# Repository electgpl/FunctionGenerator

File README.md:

# Generador de Funciones con XR2206 v1.0 

# Generador de Funciones con XR2206 v2.0 

Este es un Generador de Señales discreto en base a componentes de fácil adquisición para facilitar la producción para ser ensamblado por los estudiantes.

## Controles - v1.0

  - Generador - **XR2206**
  - Preajuste de Simetría
  - Preajuste de Distorsión
  - Ajuste de Amplitud
  - Ajuste de Ganancia
  - Ajuste de Frecuencia
  - Selección de Rango de Frecuencia mediante Jumper o switch (4 rangos)
  - Selección de salida Triangular o Senoidal mediante Jumper o switch
  - Buffer de Salida
  - Salida BNC de 50R
  - Salida Cuadrada para Frecuencímetro y Sincronismo
  
## Controles - v2.0

  - Generador - **XR2206**
  - Preajuste de Simetría
  - Preajuste de Distorsión
  - Ajuste de Amplitud
  - ~~Ajuste de Ganancia~~
  - Ajuste de Frecuencia
  - Selección de Rango de Frecuencia mediante Jumper o switch ~~(4 rangos)~~ (3 rangos)
  - Selección de salida Triangular o Senoidal mediante Jumper o switch
  - ~~Buffer de Salida~~
  - Salida BNC de 50R
  - Salida Cuadrada para Frecuencímetro y Sincronismo

## Alimentacion

> Diseñado para ser alimentado con una única batería de 9V
> en su interior cuenta con una fuente con masa flotante para lograr la simetría en el amplificador operacional (solo para v1.0).
> El amplificador operacional puede ser reemplazado por cualquiera con entrada FET (Se requiere alta impedancia) (solo para v1.0).

### Diseño

> Diseñado con EAGLE, en solo una capa con componentes THT para facilitar
> la integración al alumno, el desarrollo del PCB en el hogar y mantener
> el menor costo posible.

### Pruebas de Señal Seno y Cuadrada

### Pruebas de FFT sobre Seno

Patrocinado
----

License
----

MIT

**Free Software, Hell Yeah!**

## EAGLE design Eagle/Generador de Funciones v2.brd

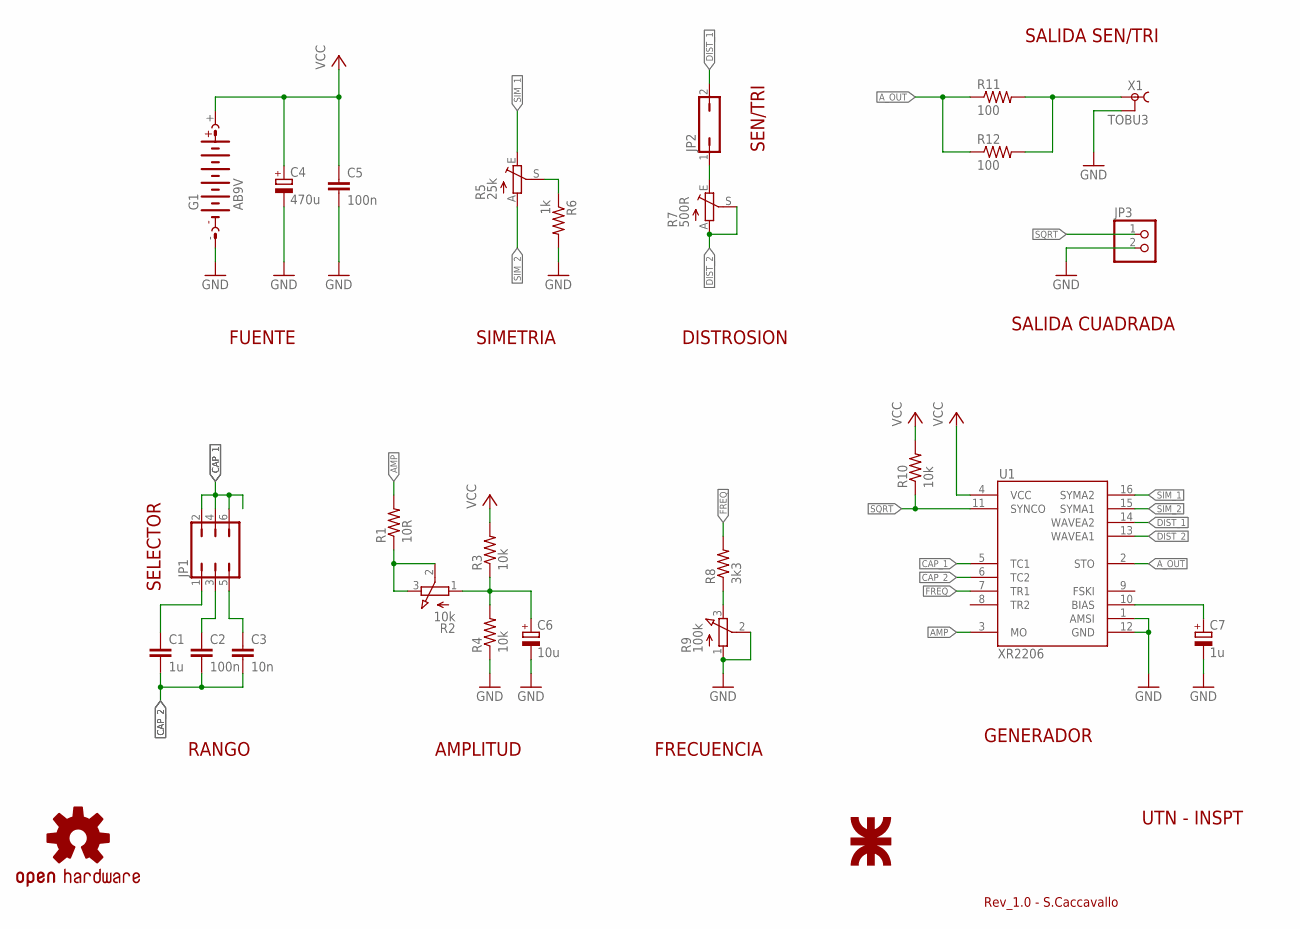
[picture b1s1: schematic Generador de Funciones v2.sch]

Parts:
C1: 1u; C050-024X044
C2, C5: 100n; C050-024X044
C3: 10n; C050-024X044
C4: 470u; E3,5-8
C6: 10u; E2,5-6
C7: 1u; E2,5-6
G1: AB9V
JP1: JP3Q
JP2: JP1Q; JP1
JP3: PINHD-1X2; 1X02
R1: 10R; 0207/10
R2: 10k; 3RP/1610N
R3, R4, R10: 10k; 0207/10
R5: 25k; RJ9W
R6: 1k; 0207/10
R7: 500R; RJ9W
R8: 3k3; 0207/10
R9: 100k; 3RP/1610N
R11, R12: 100; 0207/10
U1: XR2206; DIL16
U$1: UTN_LOGO_0; UTN_LOGO_0_TOP
U$4: OSHW-LOGOM; OSHW-LOGO-M
X1: TOBU3

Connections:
AMP: R1.2, U1.3 (MO)
A_OUT: R11.1, R12.1, U1.2 (STO)
CAP_1: JP1.2, JP1.4, JP1.6, U1.5 (TC1)
CAP_2: C1.2, C2.2, C3.2, U1.6 (TC2)
DIST_1: JP2.2, U1.14 (WAVEA2)
DIST_2: R7.A, R7.S, U1.13 (WAVEA1)
FREQ: R8.2, U1.7 (TR1)
GND: C4.-, C5.2, C6.-, C7.-, G1.-, JP3.2, R4.1, R6.2, R9.1 (A), R9.2 (S), U1.1 (AMSI), U1.12 (GND), X1.2, X1.2@1 (2), X1.2@2 (2)
unnamed: R1.1, R2.2 (S), R2.3 (E)
unnamed: R8.1, R9.3 (E)
unnamed: C1.1, JP1.1
unnamed: C2.1, JP1.3
unnamed: C7.+, U1.10 (BIAS)
unnamed: R5.S, R6.1
unnamed: C3.1, JP1.5
unnamed: R11.2, R12.2, X1.1
unnamed: JP2.1, R7.E
unnamed: C6.+, R2.1 (A), R3.1, R4.2
SIM_1: R5.E, U1.16 (SYMA2)
SIM_2: R5.A, U1.15 (SYMA1)
SQRT: JP3.1, R10.1, U1.11 (SYNCO)
VCC: C4.+, C5.1, G1.+, R3.2, R10.2, U1.4 (VCC)

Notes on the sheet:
RANGO
AMPLITUD
FRECUENCIA
SIMETRIA
DISTROSION
FUENTE
SELECTOR
SEN/TRI
UTN - INSPT
SALIDA SEN/TRI
GENERADOR
SALIDA CUADRADA
Rev_1.0 - S.Caccavallo

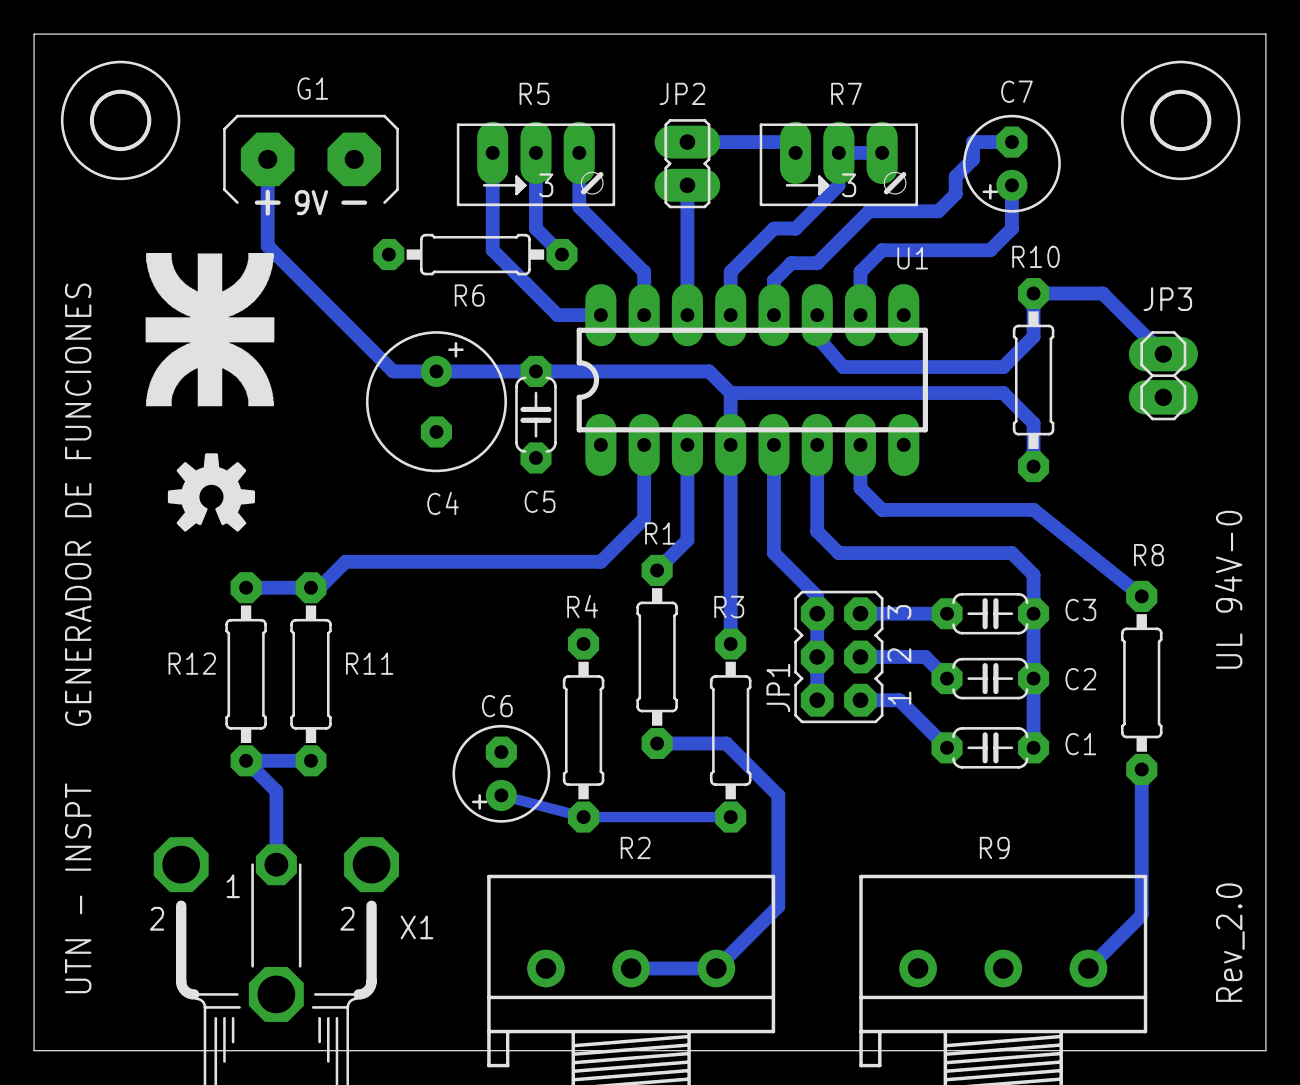
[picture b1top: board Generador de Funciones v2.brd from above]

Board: 2 copper layers, 72.3 x 59.7 mm, 29 parts (0 on the bottom side), 22 nets.

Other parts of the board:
U$2, U$3: 3,2

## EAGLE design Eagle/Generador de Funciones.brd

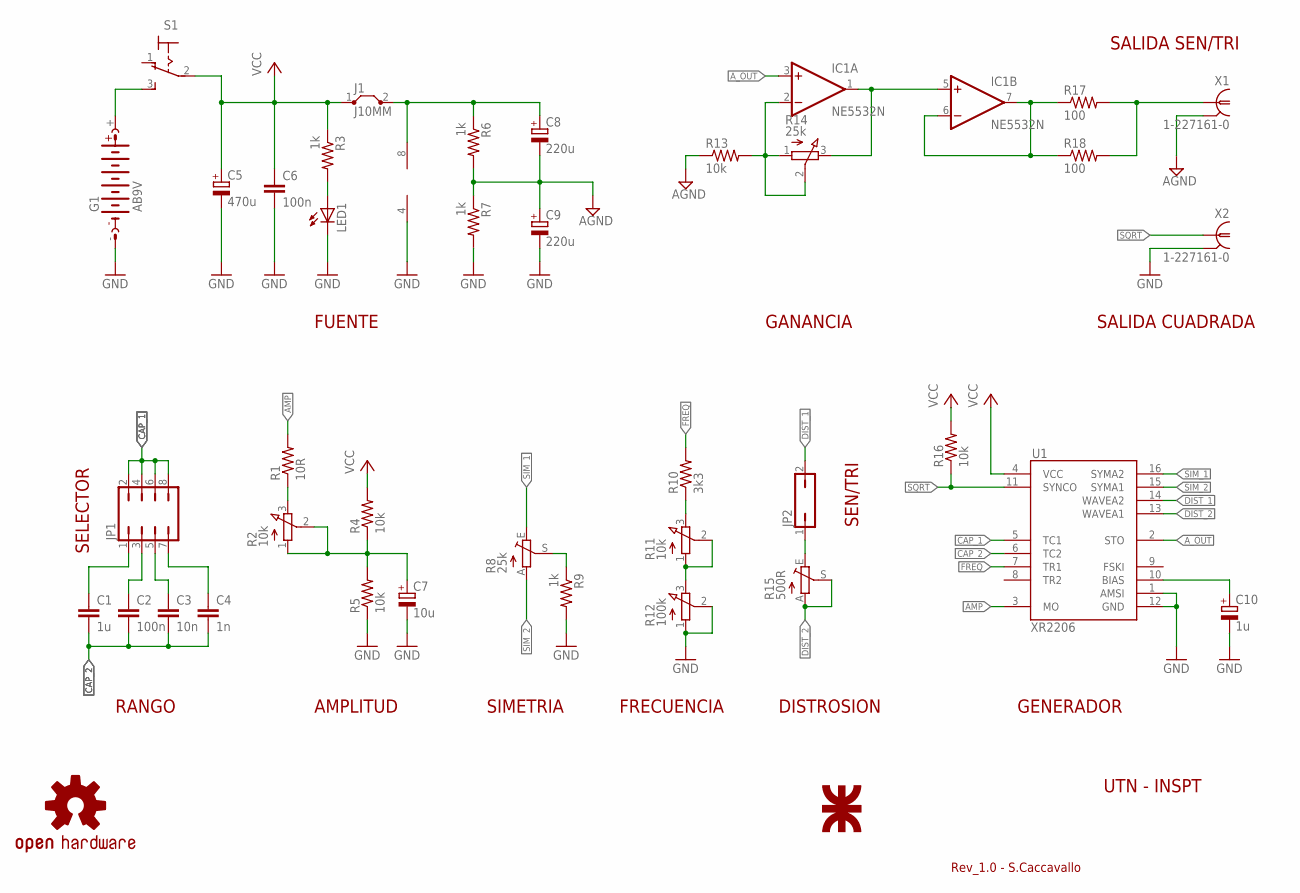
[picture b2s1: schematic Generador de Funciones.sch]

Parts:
C1: 1u; C050-024X044
C2, C6: 100n; C050-024X044
C3: 10n; C050-024X044
C4: 1n; C050-024X044
C5: 470u; E3,5-8
C7: 10u; E2,5-6
C8, C9: 220u; E3,5-8
C10: 1u; E2,5-6
G1: AB9V
IC1: NE5532N; DIL08
J1: J10MM; 10
JP1: JP4Q
JP2: JP1Q; JP1
LED1: LED5MM
R1: 10R; 0204/7
R2, R11: 10k; 3RP/1610N
R3, R6, R7, R9: 1k; 0204/7
R4, R5, R13, R16: 10k; 0204/7
R8: 25k; RJ9W
R10: 3k3; 0204/7
R12: 100k; 3RP/1610N
R14: 25k; 3RP/1610N
R15: 500R; RJ9W
R17, R18: 100; 0204/7
S1: M9040P
U1: XR2206; DIL16
U$1: UTN_LOGO_0; UTN_LOGO_0_TOP
U$4: OSHW-LOGOL; OSHW-LOGO-L
X1, X2: 1-227161-0; AMP_227161

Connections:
AGND: C8.-, C9.+, R6.2, R7.1, R13.1, X1.2
AMP: R1.2, U1.3 (MO)
A_OUT: IC1.3 (+IN), U1.2 (STO)
CAP_1: JP1.2, JP1.4, JP1.6, JP1.8, U1.5 (TC1)
CAP_2: C1.2, C2.2, C3.2, C4.2, U1.6 (TC2)
DIST_1: JP2.2, U1.14 (WAVEA2)
DIST_2: R15.A, R15.S, U1.13 (WAVEA1)
FREQ: R10.2, U1.7 (TR1)
GND: C5.-, C6.2, C7.-, C9.-, C10.-, G1.-, IC1.4 (V-), LED1.K (C), R5.1, R7.2, R9.2, R12.1 (A), R12.2 (S), U1.1 (AMSI), U1.12 (GND), X2.2
unnamed: IC1.2 (-IN), R13.2, R14.1 (A), R14.2 (S)
unnamed: R1.1, R2.3 (E)
unnamed: R11.1 (A), R11.2 (S), R12.3 (E)
unnamed: R10.1, R11.3 (E)
unnamed: C1.1, JP1.1
unnamed: C2.1, JP1.3
unnamed: C10.+, U1.10 (BIAS)
unnamed: R8.S, R9.1
unnamed: C3.1, JP1.5
unnamed: C4.1, JP1.7
unnamed: R17.2, R18.2, X1.1
unnamed: LED1.A, R3.2
unnamed: JP2.1, R15.E
unnamed: G1.+, S1.3 (S)
unnamed: C7.+, R2.1 (A), R2.2 (S), R4.1, R5.2
unnamed: IC1.1 (OUT), IC1.5 (+IN), R14.3 (E)
unnamed: IC1.6 (-IN), IC1.7 (OUT), R17.1, R18.1
unnamed: C8.+, IC1.8 (V+), J1.2, R6.1
SIM_1: R8.E, U1.16 (SYMA2)
SIM_2: R8.A, U1.15 (SYMA1)
SQRT: R16.1, U1.11 (SYNCO), X2.1
VCC: C5.+, C6.1, J1.1, R3.1, R4.2, R16.2, S1.2, U1.4 (VCC)

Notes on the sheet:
RANGO
AMPLITUD
FRECUENCIA
SIMETRIA
DISTROSION
FUENTE
SELECTOR
SEN/TRI
UTN - INSPT
SALIDA SEN/TRI
GENERADOR
SALIDA CUADRADA
GANANCIA
Rev_1.0 - S.Caccavallo

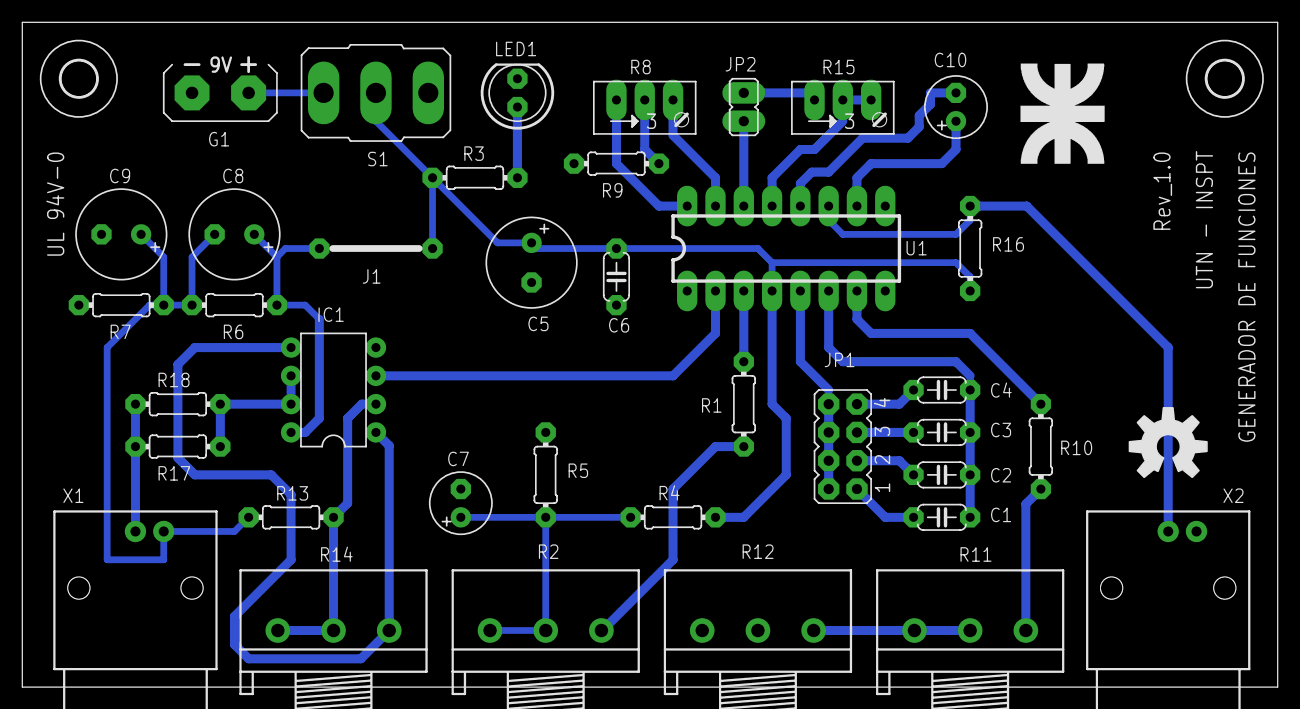
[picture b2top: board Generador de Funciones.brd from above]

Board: 2 copper layers, 112.7 x 59.7 mm, 42 parts (0 on the bottom side), 31 nets.

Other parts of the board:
U$2, U$3: 3,2

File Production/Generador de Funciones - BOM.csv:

"Qty";"Value";"Device";"Package";"Parts";"Description";"MF";"MPN";"OC_FARNELL";"OC_NEWARK";"SPICEPREFIX";
"1";"";"JP1Q";"JP1";"JP2";"JUMPER";"";"";"";"";"";
"1";"";"JP4Q";"JP4Q";"JP1";"JUMPER";"";"";"";"";"";
"1";"";"LED5MM";"LED5MM";"LED1";"LED";"";"";"";"";"";
"1";"";"PINHD-1X2";"1X02";"JP3";"PIN HEADER";"";"";"";"";"";
"1";"1-227161-0";"1-227161-0";"AMP_227161";"X1";"JACK,  RIGHT ANGLE, 50 OHM, PCB, BNC";"TYCO ELECTRONICS";"1-227161";"unknown";"33B3200";"";
"2";"100";"R-US_0204/7";"0204/7";"R17, R18";"RESISTOR, American symbol";"";"";"";"";"R";
"1";"100k";"3RP/1610N";"3RP/1610N";"R12";"16mm Potentiometer one level";"";"";"";"";"";
"2";"100n";"C-EU050-024X044";"C050-024X044";"C2, C6";"CAPACITOR, European symbol";"";"";"";"";"C";
"1";"10R";"R-US_0204/7";"0204/7";"R1";"RESISTOR, American symbol";"";"";"";"";"R";
"1";"10k";"3RP/1610N";"3RP/1610N";"R2";"16mm Potentiometer one level";"";"";"";"";"";
"4";"10k";"R-US_0204/7";"0204/7";"R4, R5, R13, R16";"RESISTOR, American symbol";"";"";"";"";"R";
"1";"10n";"C-EU050-024X044";"C050-024X044";"C3";"CAPACITOR, European symbol";"";"";"";"";"C";
"1";"10u";"CPOL-EUE2.5-6";"E2,5-6";"C7";"POLARIZED CAPACITOR, European symbol";"";"";"";"";"C";
"4";"1k";"R-US_0204/7";"0204/7";"R3, R6, R7, R9";"RESISTOR, American symbol";"";"";"";"";"R";
"1";"1n";"C-EU050-024X044";"C050-024X044";"C4";"CAPACITOR, European symbol";"";"";"";"";"C";
"1";"1u";"C-EU050-024X044";"C050-024X044";"C1";"CAPACITOR, European symbol";"";"";"";"";"C";
"1";"1u";"CPOL-EUE2.5-6";"E2,5-6";"C10";"POLARIZED CAPACITOR, European symbol";"";"";"";"";"C";
"2";"220u";"CPOL-EUE3.5-8";"E3,5-8";"C8, C9";"POLARIZED CAPACITOR, European symbol";"";"";"";"";"C";
"1";"25k";"3RP/1610N";"3RP/1610N";"R14";"16mm Potentiometer one level";"";"";"";"";"";
"1";"25k";"TRIM_EU-RJ9W";"RJ9W";"R8";"POTENTIOMETER";"";"";"";"";"";
"1";"3k3";"R-US_0204/7";"0204/7";"R10";"RESISTOR, American symbol";"";"";"";"";"R";
"1";"470u";"CPOL-EUE3.5-8";"E3,5-8";"C5";"POLARIZED CAPACITOR, European symbol";"";"";"";"";"C";
"1";"500R";"TRIM_EU-RJ9W";"RJ9W";"R15";"POTENTIOMETER";"";"";"";"";"";
"1";"AB9V";"AB9V";"AB9V";"G1";"9-V BATTERY CLIP";"";"";"";"";"";
"1";"J10MM";"J10MM";"10";"J1";"Bridge";"";"";"";"";"";
"1";"LM358N";"LM358N";"DIL08";"IC1";"OP AMP also LM158; LM258; LM2904";"";"";"";"";"";
"1";"OSHW-LOGOL";"OSHW-LOGOL";"OSHW-LOGO-L";"U$4";"Open Source Hardware Logo This logo indicates the piece of hardware it is found on incorporates a OSHW license and/or adheres to the definition of open source hardware found here: http://freedomdefined.org/OSHW";"";"";"";"";"";
"1";"UTN_LOGO_0";"UTN_LOGO_0";"UTN_LOGO_0_TOP";"U$1";"";"";"";"";"";"";
"1";"XR2206";"XR2206";"DIL16";"IC2";"XR2206 Monolithic Function Generator";"";"";"";"";"";

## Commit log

2018-07-07 Create sadasd

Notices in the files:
parts and their libraries:
SparkFun: Licensing: CC v3.0 Share-Alike You are welcome to use this library for commercial purposes.
